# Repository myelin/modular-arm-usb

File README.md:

Multi-purpose board with:

- usb type A plug
- 3v3 ldo (from usb)
- lpc11u14, swd connector, pullups, caps
- some broken-out gpio (including uart, i2c, spi)
- led (ws2812b?)
- nrf24l01+
- battery connector (or maybe just a generic power input)
- fuse

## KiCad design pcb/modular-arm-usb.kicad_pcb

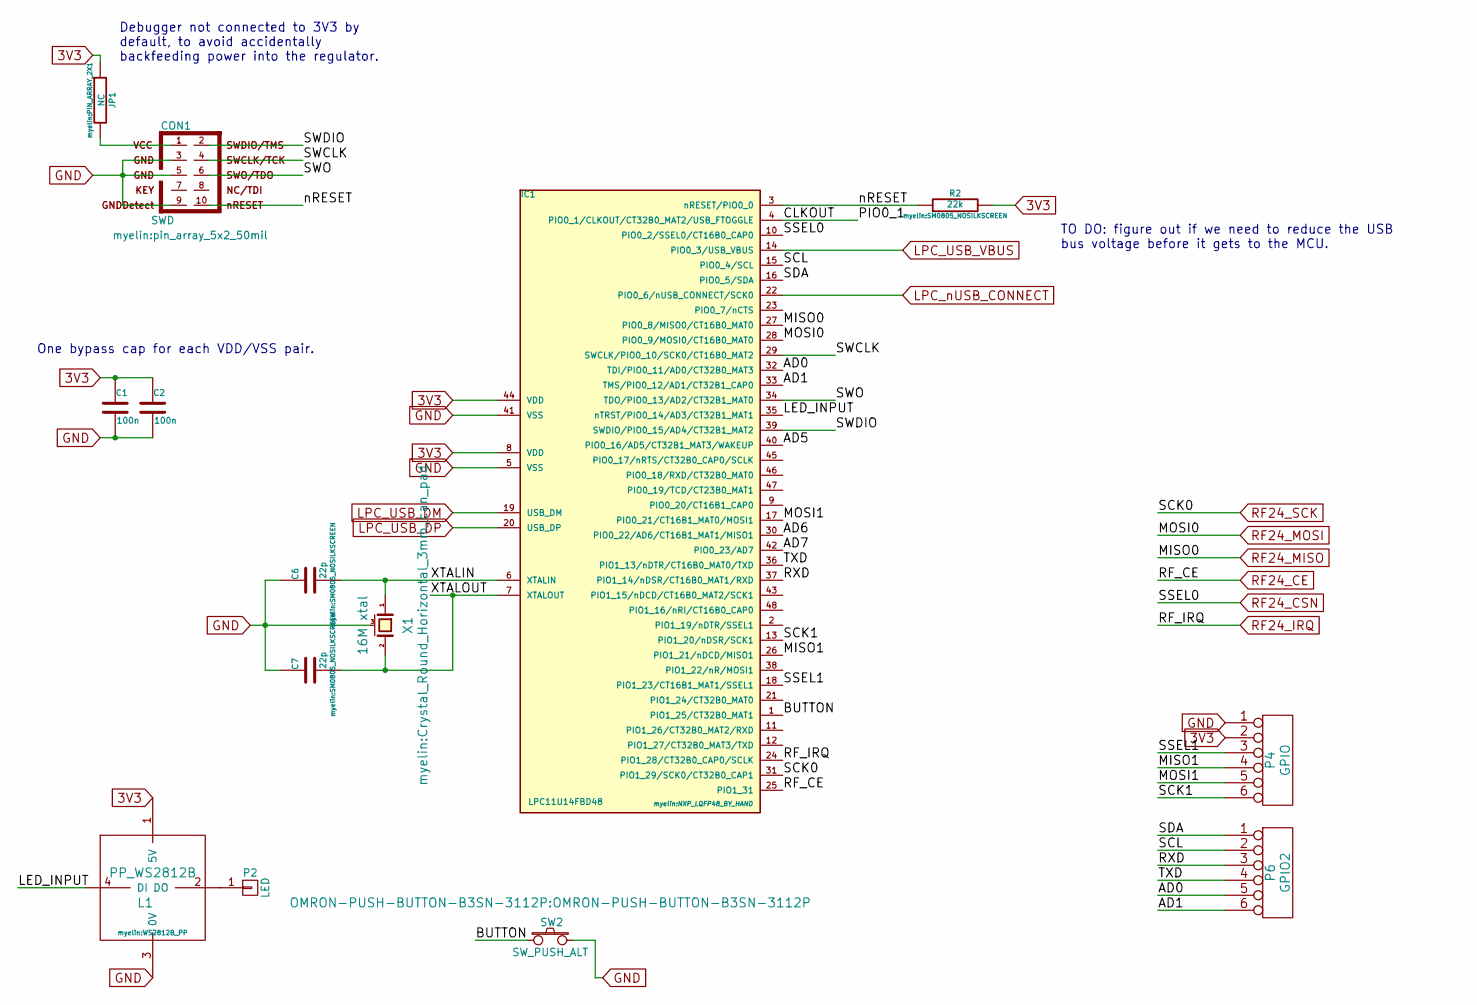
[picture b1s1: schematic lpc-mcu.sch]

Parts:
C1, C2: 100n; SM0805_NOSILKSCREEN
C6, C7: 22p; SM0805_NOSILKSCREEN
CON1: SWD; pin_array_5x2_50mil
IC1: LPC11U14FBD48; NXP_LQFP48_BY_HAND
JP1: NC; PIN_ARRAY_2X1
L1: PP_WS2812B; WS2812B_PP
P2: LED; Pin_Header_Straight_1x01
P4: GPIO; PIN_ARRAY_6X1
P6: GPIO2; PIN_ARRAY_6X1
R2: 22k; SM0805_NOSILKSCREEN
SW2: SW_PUSH_ALT; OMRON-PUSH-BUTTON-B3SN-3112P
X1: 16M xtal; Crystal_Round_Horizontal_3mm_can_pad

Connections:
3V3: C1.1, C2.1, IC1.8 (VDD), IC1.44 (VDD), JP1.1, L1.1 (5V), P4.2, R2.2; also elsewhere on the board
/lpc-mcu/AD0: IC1.32 (TDI/PIO0_11/AD0/CT32B0_MAT3), P6.5
/lpc-mcu/AD1: IC1.33 (TMS/PIO0_12/AD1/CT32B1_CAP0), P6.6
/lpc-mcu/AD5: IC1.40 (PIO0_16/AD5/CT32B1_MAT3/WAKEUP)
/lpc-mcu/AD6: IC1.30 (PIO0_22/AD6/CT16B1_MAT1/MISO1)
/lpc-mcu/AD7: IC1.42 (PIO0_23/AD7)
/lpc-mcu/BUTTON: IC1.1 (PIO1_25/CT32B0_MAT1), SW2.1
/lpc-mcu/CLKOUT: IC1.4 (PIO0_1/CLKOUT/CT32B0_MAT2/USB_FTOGGLE)
/lpc-mcu/LED_INPUT: IC1.35 (nTRST/PIO0_14/AD3/CT32B1_MAT1), L1.4 (DI)
/lpc-mcu/MISO1: IC1.26 (PIO1_21/nDCD/MISO1), P4.4
/lpc-mcu/MOSI1: IC1.17 (PIO0_21/CT16B1_MAT0/MOSI1), P4.5
/lpc-mcu/RXD: IC1.37 (PIO1_14/nDSR/CT16B0_MAT1/RXD), P6.3
/lpc-mcu/SCK1: IC1.13 (PIO1_20/nDSR/SCK1), P4.6
/lpc-mcu/SCL: IC1.15 (PIO0_4/SCL), P6.2
/lpc-mcu/SDA: IC1.16 (PIO0_5/SDA), P6.1
/lpc-mcu/SSEL1: IC1.18 (PIO1_23/CT16B1_MAT1/SSEL1), P4.3
/lpc-mcu/SWCLK: CON1.4, IC1.29 (SWCLK/PIO0_10/SCK0/CT16B0_MAT2)
/lpc-mcu/SWDIO: CON1.2, IC1.39 (SWDIO/PIO0_15/AD4/CT32B1_MAT2)
/lpc-mcu/SWO: CON1.6, IC1.34 (TDO/PIO0_13/AD2/CT32B1_MAT0)
/lpc-mcu/TXD: IC1.36 (PIO1_13/nDTR/CT16B0_MAT0/TXD), P6.4
/lpc-mcu/XTALIN: C6.2, IC1.6 (XTALIN), X1.1
/lpc-mcu/XTALOUT: C7.2, IC1.7 (XTALOUT), X1.2
/lpc-mcu/nRESET: CON1.10, IC1.3 (nRESET/PIO0_0), R2.1
GND: C1.2, C2.2, C6.1, C7.1, CON1.3, CON1.5, CON1.9, IC1.5 (VSS), IC1.41 (VSS), L1.3 (0V), P4.1, SW2.3, X1.3 (case); also elsewhere on the board
LPC_USB_DM: IC1.19 (USB_DM); also elsewhere on the board
LPC_USB_DP: IC1.20 (USB_DP); also elsewhere on the board
LPC_USB_VBUS: IC1.14 (PIO0_3/USB_VBUS)
LPC_nUSB_CONNECT: IC1.22 (PIO0_6/nUSB_CONNECT/SCK0)
unnamed: CON1.1, JP1.2
unnamed: L1.2 (DO), P2.1
RF24_CE: IC1.25 (PIO1_31); also elsewhere on the board
RF24_CSN: IC1.10 (PIO0_2/SSEL0/CT16B0_CAP0); also elsewhere on the board
RF24_IRQ: IC1.24 (PIO1_28/CT32B0_CAP0/SCLK); also elsewhere on the board
RF24_MISO: IC1.27 (PIO0_8/MISO0/CT16B0_MAT0); also elsewhere on the board
RF24_MOSI: IC1.28 (PIO0_9/MOSI0/CT16B0_MAT0); also elsewhere on the board
RF24_SCK: IC1.31 (PIO1_29/SCK0/CT32B0_CAP1); also elsewhere on the board

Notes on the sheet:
Debugger not connected to 3V3 by default, to avoid accidentally backfeeding power into the regulator.
One bypass cap for each VDD/VSS pair.
TO DO: figure out if we need to reduce the USB bus voltage before it gets to the MCU.

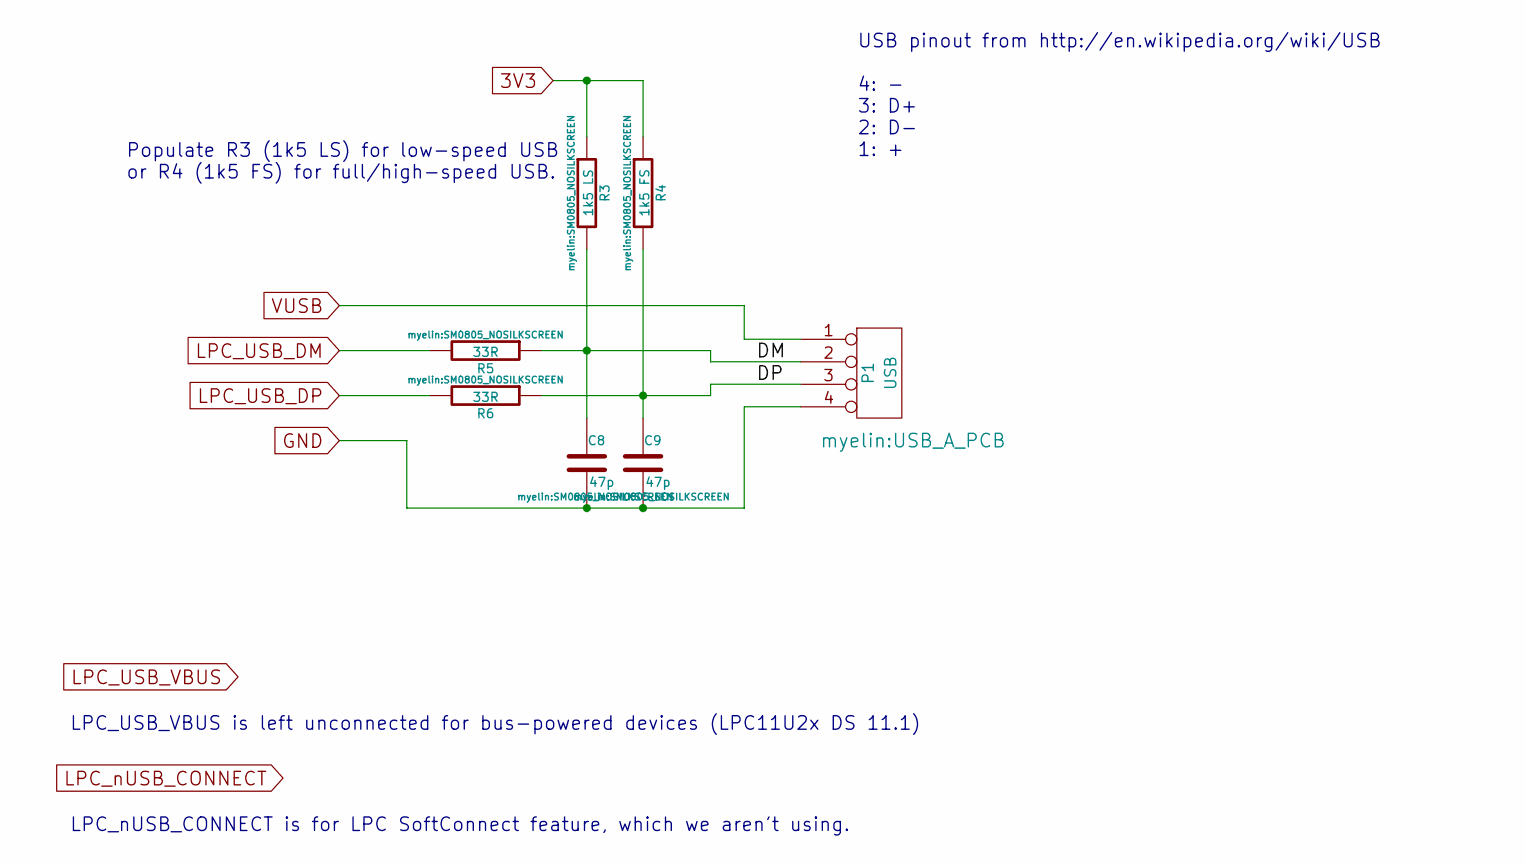
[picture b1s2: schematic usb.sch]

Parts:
C8, C9: 47p; SM0805_NOSILKSCREEN
P1: USB; USB_A_PCB
R3: 1k5 LS; SM0805_NOSILKSCREEN
R4: 1k5 FS; SM0805_NOSILKSCREEN
R5, R6: 33R; SM0805_NOSILKSCREEN

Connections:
3V3: R3.1, R4.1; also elsewhere on the board
/usb/DM: C8.1, P1.2, R3.2, R5.1
/usb/DP: C9.1, P1.3, R4.2, R6.1
GND: C8.2, C9.2, P1.4; also elsewhere on the board
LPC_USB_DM: R5.2; also elsewhere on the board
LPC_USB_DP: R6.2; also elsewhere on the board
VUSB: P1.1; also elsewhere on the board

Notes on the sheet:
LPC_nUSB_CONNECT is for LPC SoftConnect feature, which we aren't using.
LPC_USB_VBUS is left unconnected for bus-powered devices (LPC11U2x DS 11.1)
USB pinout from http://en.wikipedia.org/wiki/USB 4: - 3: D+ 2: D- 1: +
Populate R3 (1k5 LS) for low-speed USB or R4 (1k5 FS) for full/high-speed USB.

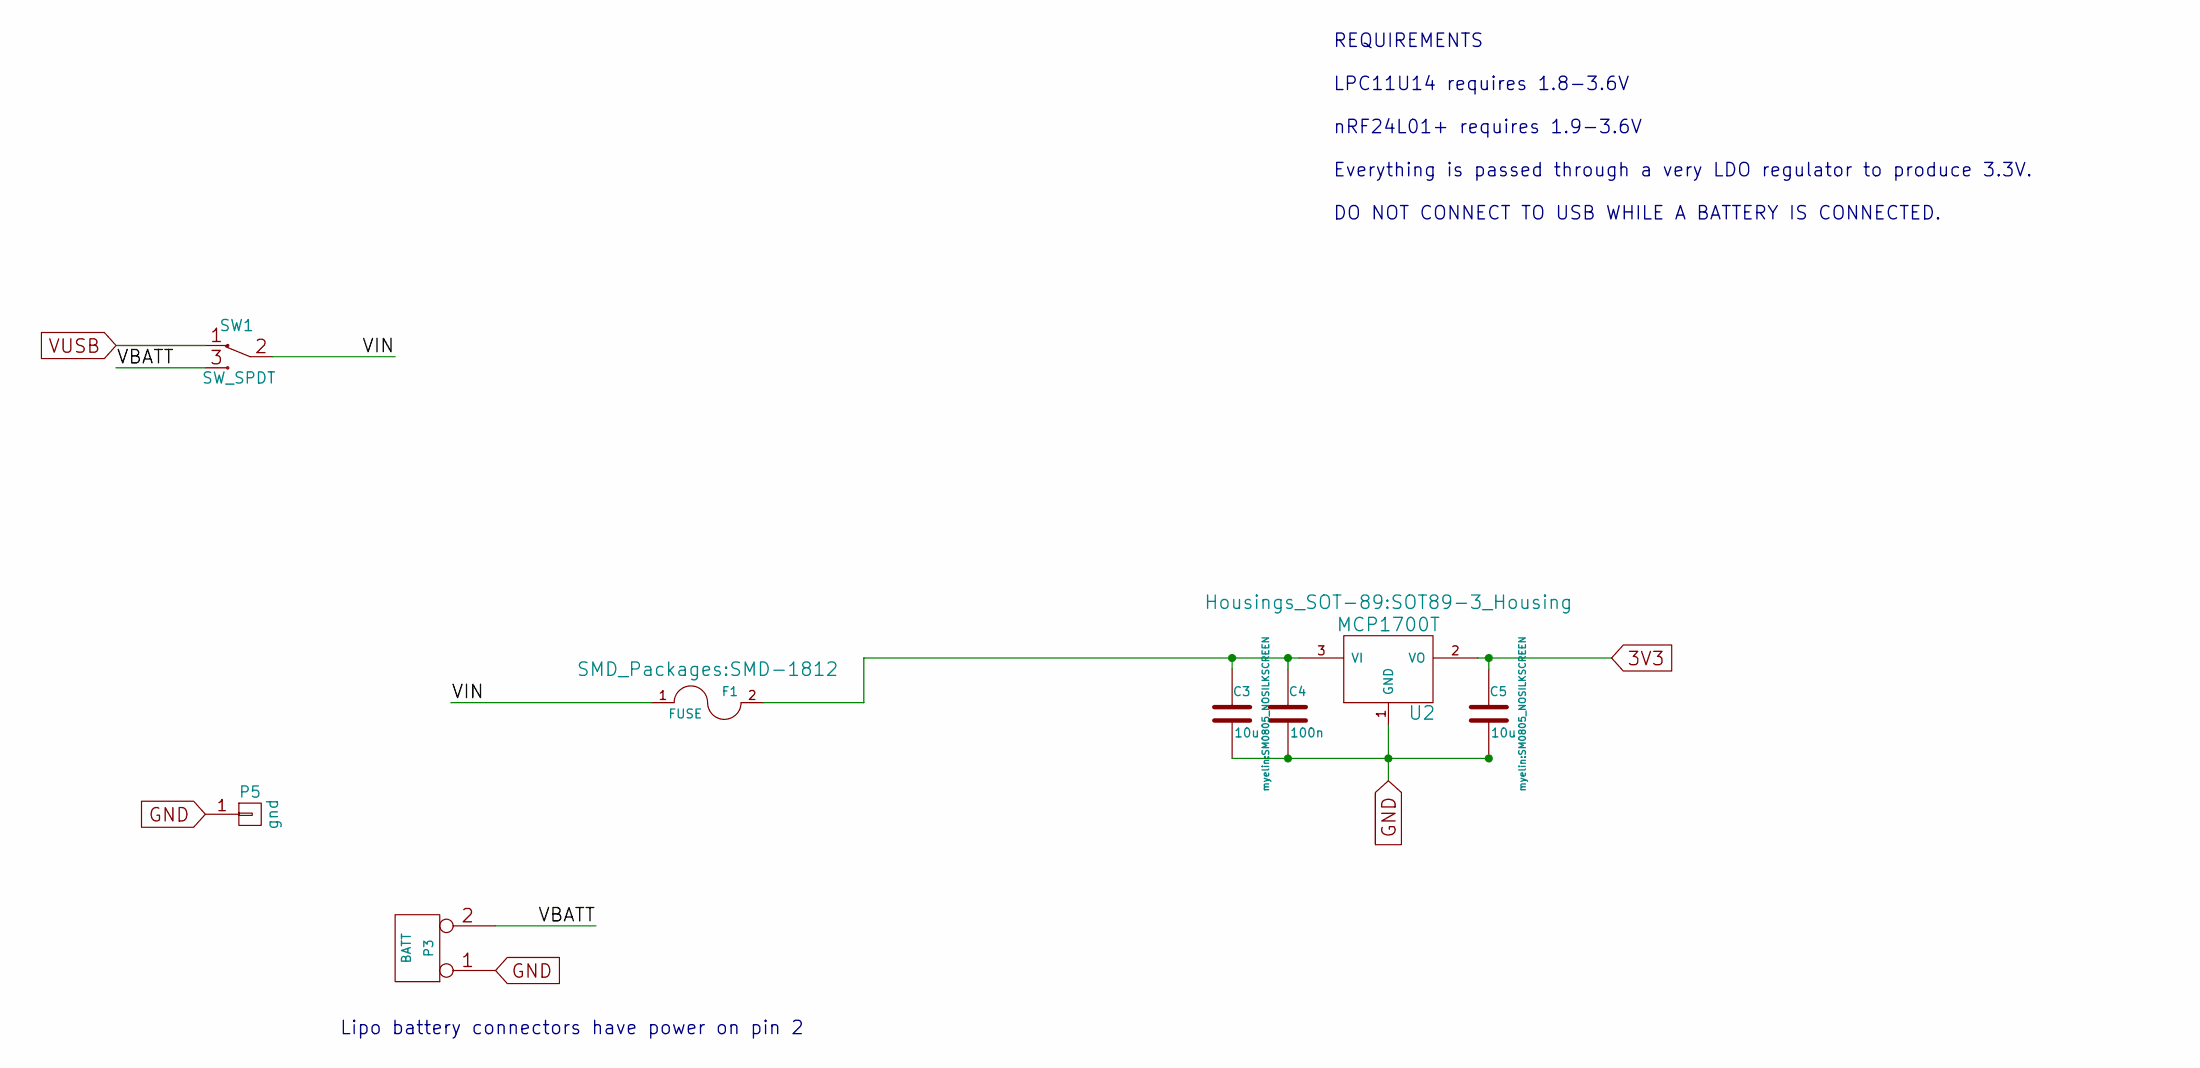
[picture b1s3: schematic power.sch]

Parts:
C3, C5: 10u; SM0805_NOSILKSCREEN
C4: 100n; SM0805_NOSILKSCREEN
F1: FUSE; SMD-1812
P3: BATT; S2B-PH-SM4-TB(LF)(SN)
P5: gnd; Pin_Header_Straight_1x01
SW1: SW_SPDT; PIN_ARRAY_3X1
U2: MCP1700T; SOT89-3_Housing

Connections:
3V3: C5.1, U2.2 (VO); also elsewhere on the board
/power/VBATT: P3.2 (PM), SW1.3 (NO)
/power/VIN: F1.1, SW1.2 (COM)
GND: C3.2, C4.2, C5.2, P3.1, P5.1, U2.1 (GND); also elsewhere on the board
unnamed: C3.1, C4.1, F1.2, U2.3 (VI)
VUSB: SW1.1 (NC); also elsewhere on the board

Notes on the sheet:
Lipo battery connectors have power on pin 2
REQUIREMENTS LPC11U14 requires 1.8-3.6V nRF24L01+ requires 1.9-3.6V Everything is passed through a very LDO regulator to produce 3.3V. DO NOT CONNECT TO USB WHILE A BATTERY IS CONNECTED.

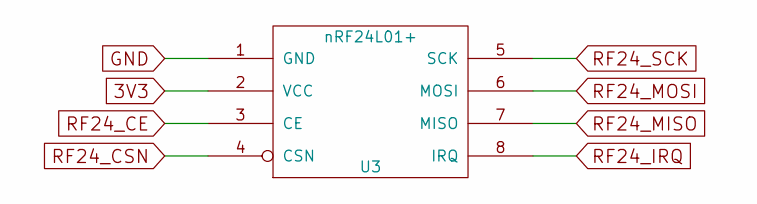
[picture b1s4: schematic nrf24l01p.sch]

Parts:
U3: nRF24L01+; NRF24L01_MODULE

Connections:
3V3: U3.2 (VCC); also elsewhere on the board
GND: U3.1 (GND); also elsewhere on the board
RF24_CE: U3.3 (CE); also elsewhere on the board
RF24_CSN: U3.4 (CSN); also elsewhere on the board
RF24_IRQ: U3.8 (IRQ); also elsewhere on the board
RF24_MISO: U3.7 (MISO); also elsewhere on the board
RF24_MOSI: U3.6 (MOSI); also elsewhere on the board
RF24_SCK: U3.5 (SCK); also elsewhere on the board

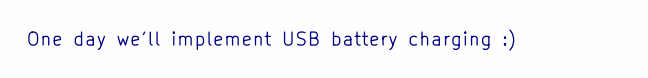
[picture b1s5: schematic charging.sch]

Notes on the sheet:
One day we'll implement USB battery charging :)

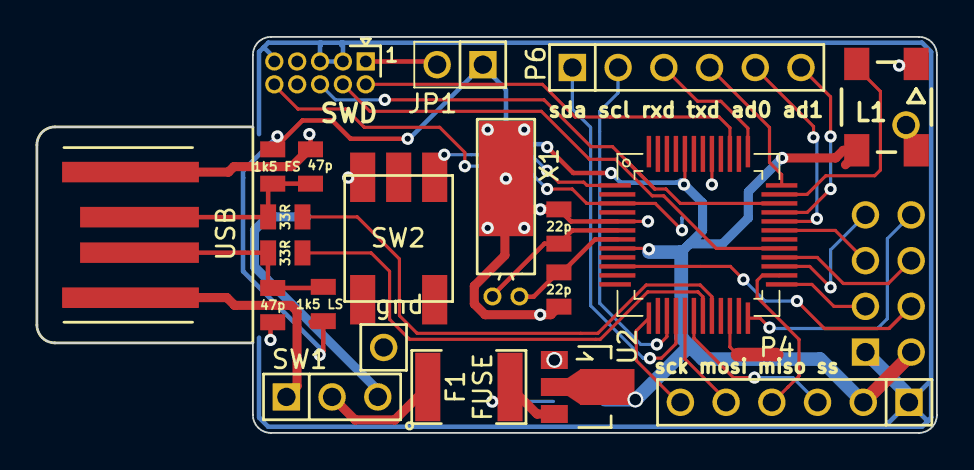
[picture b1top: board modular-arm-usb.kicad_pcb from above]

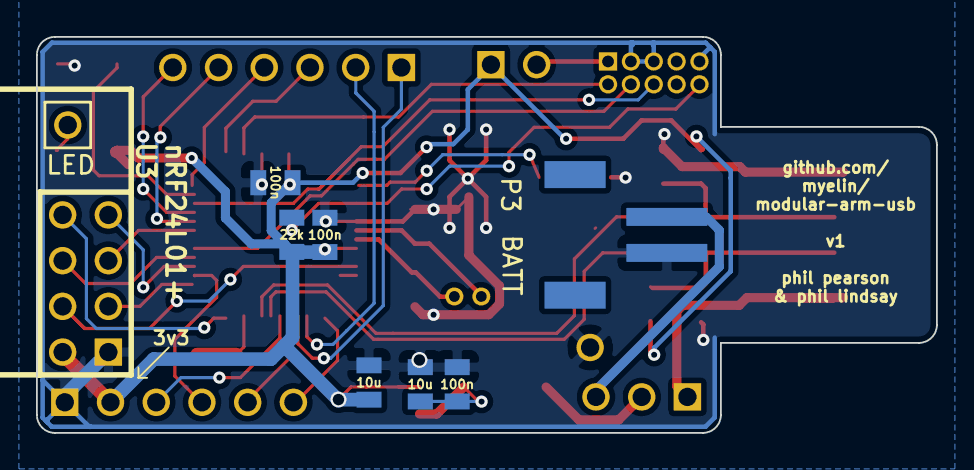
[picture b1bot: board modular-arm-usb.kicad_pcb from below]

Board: 2 copper layers, 50.0 x 22.0 mm, 30 parts (9 on the bottom side), 36 nets.

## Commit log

2014-12-26 initial import - blank project
2014-12-26 added readme
2014-12-26 created sheets for modules
2014-12-26 some modules and libraries we'll want
2014-12-26 added ARM SWD header library
2014-12-26 first cut of the power system
2014-12-26 JST PH battery connector
2014-12-26 started on lpc-mcu and ucb sheets
2014-12-26 moved everything into follower's preferred project layout
2014-12-26 put nrf24l01p.sch into the proper place in the hierarchy
2014-12-26 added SWD connector
2014-12-26 added reset pullup, some caps, usb resistors, explanation for nUSB_CONNECT
2014-12-26 tied up some loose ends in power.sch
2014-12-26 thought through power situation a bit more, added some TO DO messages
2014-12-26 added second 3v3 ldo in parallel with the first one, so we can have the option at build time
2014-12-26 made a usb-a plug from usb-if and wikipedia docs
2014-12-27 made a footprint for the lpc11u14 that should be nice to hand solder
2014-12-27 pulled in regulator footprint, started on pcb
2014-12-27 power and usb - a bit more progress
2014-12-27 added LED, and removed VLED from power sheet
2014-12-27 some labels, and changed sm0805 parts to use my nosilkscreen package
2014-12-27 gpios and rf24 connections
2014-12-27 Add footprints from <http://smisioto.no-ip.org/kicad_libs/modules/mod_smd_trans.zip> for SOT23.
2014-12-27 Add the footprint library with SOT23 to the project.
2014-12-27 Duplicate the SOT23 footprint to SOT23-ALT to change the pin numbers (this may not be necessary just to change the pin numbering?).
2014-12-27 Modify the SOT23 pinout to match the alternate numbering used by LM3480.
2014-12-27 Add symbols from <http://smisioto.no-ip.org/kicad_libs/library/lib_w_analog.zip> to use as base for LM3480 symbol.
2014-12-27 Add LM3480 symbol (based on an existing symbol from the library). TODO: Separate out? Submit PR to original project? NOTE: Not yet tested.
2014-12-28 added .gitattributes that specifies native line endings for pretty much everything
2014-12-28 switched everything to native line endings
2014-12-28 fixed line endings on the last couple of files, and copied in my standard .gitignore
2015-01-03 updated kicad to latest version and fixed things that didn't show up properly (text, nrf24l01+ part)
2015-01-04 Upgraded all modules to new kicad_mod/pretty format. Added MCP1700T-3302 regulator and cleaned up power circuit. Getting closer to final power/USB placement.
2015-01-05 Add module for FabLab standard Omron Push Button from my previous project at <https://github.com/follower/led-spinner-toy/blob/master/pcb/parts/rancidbacon/OMRON-PUSH-BUTTON-B3SN-3112P.mod>.
2015-01-05 Import discrete device/components library from <http://smisioto.no-ip.org/kicad_libs/library/lib_w_device.zip> version (22/06/2013).
2015-01-05 Add the alternate pinout push button that I originally created for the reaction tester game project from the <http://smisioto.no-ip.org/> device library.
2015-01-06 moved things around on the pcb a bit, made it more compact
2015-01-10 Add reference to alternate pushbutton symbol.
2015-01-10 Add pushbutton to schematic. Usign Pin 36 currently because it's a currently unused corner pin facing away from currently routed part of the PCB.
2015-01-10 Let the pushbutton symbol be added to the cache for completeness.
2015-01-10 Add reference to pushbutton switch library footprint to footprint tables.
2015-01-10 Add device library reference for source of switch.
2015-01-10 Add power choice slide switch to the schematic.
2015-01-10 Let the slide switch symbol be added to the cache.
2015-01-13 pcb work from last night
2015-01-14 moved TXD and RXD to pins that give shorter traces, and attempted to route USB_CONNECT / implement SoftConnect, but gave up
2015-01-14 added a big empty track segment in case we want access to USB_CONNECT in an emergency
2015-01-14 gerbers for oshpark order
